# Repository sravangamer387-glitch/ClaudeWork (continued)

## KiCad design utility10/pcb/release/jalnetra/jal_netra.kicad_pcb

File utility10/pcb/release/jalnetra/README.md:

# Jal-Netra ultrasonic flow main board (rev A)

Jal-Netra main board: STM32G431 transit-time measurement (bridge-driven piezo, input mux, two-stage low-noise receive chain, gain select, 12-bit 4 MS/s ADC), USB-C powered, OLED/UART/SWD.

**Status: engineering release, software-verified only (ERC on the netlist, KiCad DRC, netlist cross-check, SPICE where noted). Not yet built, not reviewed by a second engineer, not certified.**

## Specification
- Board 86 x 66 mm, 2 layers, 1.6 mm FR-4, 1 oz copper, rounded corners R2.5 mm, 4 x M2.5 mounting holes, 2 fiducials.
- Rules used: min track 0.2 mm (power 0.4 mm), min clearance 0.15 mm, via 0.6/0.3 mm, GND pour on both layers, 128 stitching vias.
- Finish: ENIG recommended (HASL lead-free acceptable); green mask, white silk; IPC class 2.
- 78 parts, 51 nets.

## Circuit description
- **Transmit:** TIM3 channels on PA6/PA4 (transducer A) and PB0/PB1 (transducer B) generate a 6-cycle 1 MHz burst; the second pin of each pair is inverted for bridge drive (6.6 Vpp). 22 ohm series resistors protect the pins; on receive one leg is held low by its timer pin and the other is high-impedance.
- **Receive:** 10 nF + 1 k tap from the transducer's high leg, BAV99 clamp to the rails, TS5A3159 selects transducer A or B into LNA1 (OPA356, x10.2) and LNA2 (x10.2); TS5A3159 U7 selects 20 dB or 40 dB into a 33 ohm / 22 pF filter and ADC1 (PA0). Mid-supply bias 1.65 V from AVDD (ferrite-filtered 3.3 V).
- **Rest:** STM32G431CBT6 with 8 MHz crystal, SWD header, boot0 pull-down, USB-C power-only (5.1 k CC, PTC, TVS), AP2112K-3.3, OLED and UART headers, buzzer, LED, test button, test points on the receive chain.

### Simulation: `../../jal-netra/sim/lna_results.txt`
```
SPICE (ngspice) of the receive chain, source impedance 270 ohm (piezo at 1 MHz), OPA356-class model (A0 1e5, GBW 200 MHz):
stage 1 gain at 1 MHz        = 20.1 dB (target 20 dB)
stage 1 + 2 gain at 1 MHz   = 40.9 dB (target 40 dB)
stage 1 upper -3 dB          = 20 MHz
stage 1 + 2 band (-3 dB)      = 1.5 kHz ... 14 MHz
```

## Power
MCU 170 MHz about 35 mA while measuring (0.5 s per measurement), LNAs 2 x 8 mA: USB powered only (about 0.1 W average with a 10 s idle period).

## Verification
| Check | Result |
|---|---|
| Electrical rule check on the netlist (own ERC: unconnected pins, single-pin nets, output conflicts, unpowered supplies, symbol/footprint pin match) | 0 errors, 0 warnings |
| KiCad DRC | 0 errors, 0 warnings; unconnected pads: 0 |
| Schematic netlist equals PCB netlist | yes |
| Router failures | 0 |
| 3D STEP export | yes |
| Independent Gerber parse (gerbonara): layers parsed, outline size equals the design | 9 layers, outline [86.1, 66.1] mm, match |

Enclosure (prototype shell for 3D printing): outer 91.2 x 71.2 x 20.6 mm, collision/opening check: pass

## Bill of materials
| Ref | Value | Footprint | Manufacturer part | LCSC # | LCSC status |
|---|---|---|---|---|---|
| U1 | STM32G431CBT6 | LQFP-48_7x7mm_P0.5mm | STM32G431CBT6 (LQFP-48) | C529355 | verified |
| U4 | TS5A3159 | SOT-363_SC-70-6 | TI TS5A3159DCKR | C46388 | verified |
| U5 | OPA356 | SOT-23-5 | TI OPA356AIDBVR | C183100 | verified |
| U6 | OPA356 | SOT-23-5 | TI OPA356AIDBVR | C183100 | verified |
| U7 | TS5A3159 | SOT-363_SC-70-6 | TI TS5A3159DCKR | C46388 | verified |
| U3 | AP2112K-3.3 | SOT-23-5 | Diodes AP2112K-3.3TRG1 (from the LCSC datasheet link) | C51118 | verified |
| FB1 | BLM18 600R | L_0603_1608Metric | Murata BLM18AG601SN1D | C19330 | verified |
| Y1 | 8 MHz | Crystal_SMD_3225-4Pin_3.2x2.5mm | YXC X32258MOB4SI 8 MHz 12 pF 3225 (matches the 15 pF load caps) | C2682775 | verified |
| D5 | BAV99 | SOT-23 | JSCJ BAV99 | C68983 | verified |
| D6 | BAV99 | SOT-23 | JSCJ BAV99 | C68983 | verified |
| J6 | Transducer A (BTL) | JST_PH_B2B-PH-K_1x02_P2.00mm_Vertical | JST B2B-PH-K-S(LF)(SN) | C131337 | verified |
| J7 | Transducer B (BTL) | JST_PH_B2B-PH-K_1x02_P2.00mm_Vertical | JST B2B-PH-K-S(LF)(SN) | C131337 | verified |
| R30 | 22 | R_0603_1608Metric | UNI-ROYAL 0603WAF220JT5E | C23345 | verified |
| R31 | 22 | R_0603_1608Metric | UNI-ROYAL 0603WAF220JT5E | C23345 | verified |
| R32 | 22 | R_0603_1608Metric | UNI-ROYAL 0603WAF220JT5E | C23345 | verified |
| R33 | 22 | R_0603_1608Metric | UNI-ROYAL 0603WAF220JT5E | C23345 | verified |
| C20 | 10n | C_0603_1608Metric | Samsung CL10B103KB8NNNC 0603 10nF X7R 50V | C1589 | verified |
| R35 | 1k | R_0603_1608Metric | 0603 1k 1% | C21190 | verified |
| C21 | 10n | C_0603_1608Metric | Samsung CL10B103KB8NNNC 0603 10nF X7R 50V | C1589 | verified |
| R36 | 1k | R_0603_1608Metric | 0603 1k 1% | C21190 | verified |
| C22 | 100n | C_0603_1608Metric | Samsung CL10B104KB8NNNC 0603 100nF X7R 50V | C1591 | verified |
| C23 | 100n | C_0603_1608Metric | Samsung CL10B104KB8NNNC 0603 100nF X7R 50V | C1591 | verified |
| C24 | 100n | C_0603_1608Metric | Samsung CL10B104KB8NNNC 0603 100nF X7R 50V | C1591 | verified |
| C25 | 1u | C_0603_1608Metric | 0603 1uF X7R | C15849 | verified |
| R10 | 10k | R_0603_1608Metric | 0603 10k 1% | C25804 | verified |
| R11 | 10k | R_0603_1608Metric | 0603 10k 1% | C25804 | verified |
| C27 | 1u | C_0603_1608Metric | 0603 1uF X7R | C15849 | verified |
| C28 | 10n | C_0603_1608Metric | Samsung CL10B103KB8NNNC 0603 10nF X7R 50V | C1589 | verified |
| R12 | 100k | R_0603_1608Metric | 0603 100k 1% | C25803 | verified |
| R13 | 2.2k | R_0603_1608Metric | 0603 2.2k 1% | C4190 | verified |
| R14 | 240 | R_0603_1608Metric | UNI-ROYAL 0603WAF2400T5E (JLCPCB listing) | C23350 | verified |
| C29 | 1u | C_0603_1608Metric | 0603 1uF X7R | C15849 | verified |
| R15 | 0 | R_0603_1608Metric | UNI-ROYAL 0603WAF0000T5E | C21189 | verified |
| C30 | 10n | C_0603_1608Metric | Samsung CL10B103KB8NNNC 0603 10nF X7R 50V | C1589 | verified |
| R16 | 100k | R_0603_1608Metric | 0603 100k 1% | C25803 | verified |
| R17 | 1k | R_0603_1608Metric | 0603 1k 1% | C21190 | verified |
| R18 | 100 | R_0603_1608Metric | UNI-ROYAL 0603WAF1000T5E | C22775 | verified |
| C31 | 1u | C_0603_1608Metric | 0603 1uF X7R | C15849 | verified |
| R19 | 0 | R_0603_1608Metric | UNI-ROYAL 0603WAF0000T5E | C21189 | verified |
| R20 | 33 | R_0603_1608Metric | UNI-ROYAL 0603WAF330JT5E | C23140 | verified |
| C32 | 22p | C_0603_1608Metric | Samsung CL10C220JB8NNNC C0G | C1653 | verified |
| C1 | 100n | C_0603_1608Metric | Samsung CL10B104KB8NNNC 0603 100nF X7R 50V | C1591 | verified |
| C2 | 100n | C_0603_1608Metric | Samsung CL10B104KB8NNNC 0603 100nF X7R 50V | C1591 | verified |
| C3 | 100n | C_0603_1608Metric | Samsung CL10B104KB8NNNC 0603 100nF X7R 50V | C1591 | verified |
| C4 | 100n | C_0603_1608Metric | Samsung CL10B104KB8NNNC 0603 100nF X7R 50V | C1591 | verified |
| C33 | 100n | C_0603_1608Metric | Samsung CL10B104KB8NNNC 0603 100nF X7R 50V | C1591 | verified |
| C34 | 4.7u | C_0603_1608Metric | Samsung CL10A475KP8NNNC X5R 10V | C1705 | verified |
| C35 | 15p | C_0603_1608Metric | Samsung CL10C150JB8NNNC C0G | C1644 | verified |
| C36 | 15p | C_0603_1608Metric | Samsung CL10C150JB8NNNC C0G | C1644 | verified |
| R21 | 10k | R_0603_1608Metric | 0603 10k 1% | C25804 | verified |
| R22 | 10k | R_0603_1608Metric | 0603 10k 1% | C25804 | verified |
| C37 | 100n | C_0603_1608Metric | Samsung CL10B104KB8NNNC 0603 100nF X7R 50V | C1591 | verified |
| C38 | 1u | C_0603_1608Metric | 0603 1uF X7R | C15849 | verified |
| C39 | 1u | C_0603_1608Metric | 0603 1uF X7R | C15849 | verified |
| J4 | OLED I2C | JST_PH_B4B-PH-K_1x04_P2.00mm_Vertical | JST B4B-PH-K-S(LF)(SN) | C131334 | verified |
| R23 | 4.7k | R_0603_1608Metric | 0603 4.7k 1% | C23162 | verified |
| R24 | 4.7k | R_0603_1608Metric | 0603 4.7k 1% | C23162 | verified |
| J5 | UART host / BLE | JST_PH_B4B-PH-K_1x04_P2.00mm_Vertical | JST B4B-PH-K-S(LF)(SN) | C131334 | verified |
| J3 | SWD | PinHeader_2x03_P2.54mm_Vertical | HCTL PZ254-2-03-Z-8.5 (ZHOURI C5116479 had only 340 in stock) | C2894964 | verified |
| SW2 | Test / zero | SW_SPST_B3U-1000P | Omron B3U-1000P | C231329 | verified |
| TP1 | TP | TestPoint_Pad_D1.5mm |  |  |  |
| TP2 | TP | TestPoint_Pad_D1.5mm |  |  |  |
| TP3 | TP | TestPoint_Pad_D1.5mm |  |  |  |
| TP4 | TP | TestPoint_Pad_D1.5mm |  |  |  |
| TP5 | TP | TestPoint_Pad_D1.5mm |  |  |  |
| TP6 | TP | TestPoint_Pad_D1.5mm |  |  |  |
| J1 | USB-C 5V | USB_C_Receptacle_HRO_TYPE-C-31-M-12 | TYPE-C-31-M-12 | C165948 | verified |
| F1 | PTC 500mA | Fuse_1206_3216Metric | Littelfuse 1206L050YR (6 V) | C163512 | verified |
| D3 | SMAJ5.0A | D_SMA | Littelfuse SMAJ5.0A | C83329 | verified |
| R1 | 5.1k | R_0603_1608Metric | 0603 5.1k 1% | C23186 | verified |
| R2 | 5.1k | R_0603_1608Metric | 0603 5.1k 1% | C23186 | verified |
| C5 | 10u | C_0805_2012Metric | 0805 10uF X5R | C15850 | verified |
| BZ1 | Buzzer | Buzzer_12x9.5RM7.6 | YUEXIN KC1206 16 ohm passive magnetic 12x9.5 mm (2048 Hz) | C781869 | verified |
| Q1 | MMBT3904 | SOT-23 | MMBT3904 | C20526 | verified |
| D2 | 1N4148WS | D_SOD-323 | 1N4148WS | C2128 | verified |
| R7 | 1k | R_0603_1608Metric | 0603 1k 1% | C21190 | verified |
| D1 | Green | LED_0603_1608Metric | Hubei KENTO KT-0603YG yellow-green 570 nm, Vf about 2 V (lights well from 3.3 V with 1 k; the Everlight 19-217 green was out of stock) | C2289 | verified |
| R5 | 1k | R_0603_1608Metric | 0603 1k 1% | C21190 | verified |

`verified` = LCSC number confirmed by web search on 2026-10-31/11-01; `memory` = from my recollection, **check on lcsc.com before ordering**; empty = no number chosen (through-hole connectors, switches, buzzer, test points: hand-assembled or chosen by the buyer). `*_JLC_BOM.csv` / `*_JLC_CPL.csv` list only the parts with an LCSC number; JLCPCB rotation corrections (CPL) must be checked in their viewer.

## Assembly notes
- Reflow (JLCPCB SMT): all SMD parts with an LCSC number. Hand-solder: JST connectors, pin headers, buzzer, switches, test points as listed in the BOM. Fiducials and mounting holes are in the Gerbers.
- Polarity: LED cathode toward GND (silk marks), electrolytic none, diode D2 cathode to +V, Q2 orientation as footprint (SOT-23 pin 1 = gate).
- Programming: ISP header J2 (pin 1 = MISO, square pad). Flash the matching image from `utility10/firmware/release/`: Seeti Counter `4MHz/seeti_prod.hex` (production firmware: timer-triggered 16 kS/s ADC, scan mode to find the real whistle frequency, battery check), Rain Alert `8MHz/rain_alert.hex`, Bijli Meter Reader `8MHz/bijli_meter.hex` (demo-grade firmware, to be hardened).

## Bring-up and test
1. USB-C 5 V: +3V3 = 3.3 V, AVDD = 3.28 V, VMID = 1.64 V.
2. Flash over SWD; with the spool dry nothing should be received (amplitude near zero); fill with water: a burst of amplitude A appears at ADC_IN 40.5 us after the transmit edge (TP5).
3. Follow `jal-netra/docs/TEST_PLAN.md` gates 1-3.

## Files
`1_fabrication/` Gerber + drill zip (upload to JLCPCB/any fab), fab notes, copper plot
`2_assembly/` JLC BOM + CPL (SMD parts JLC assembles), full BOM with LCSC numbers for every part, pick-and-place, assembly drawing
`3_design/` KiCad 7 project (pcb, schematic, libs), netlist, STEP model, schematic PDF, renders
`4_enclosure/` printable base and lid STL
`5_verification/` DRC, ERC, verification and readiness reports

## Known limits and review checklist
- Layout was produced by a custom router and software placement; a human layout review (analog routing, ground returns, creepage, connector mechanics, silkscreen) is still required.
- Not verified: EMC, ESD (apart from TVS parts where fitted), thermal, real component tolerances, supplier stock/price, assembly house design-for-manufacture check (run JLCPCB's DFM check on the Gerbers).
- Firmware thresholds are placeholders to be calibrated on prototypes.

## Manufacturing readiness (automatic check)

| Check | Result |
|---|---|
| gerber layers and drill present | PASS |
| drc errors 0 | PASS |
| unconnected 0 | PASS |
| netlist matches schematic | PASS |
| erc errors 0 | PASS |
| independent gerber check clean | PASS |
| every part has lcsc number | PASS |
| every lcsc number verified | PASS |
| cpl rows equal jlc bom parts | PASS |
| step model | PASS |
| KiCad DRC warnings | 0 |
| **Order ready** | **YES** |

Order steps: (1) upload `1_fabrication/*_gerbers.zip`; (2) for assembly upload `2_assembly/*_JLC_BOM.csv` and `*_JLC_CPL.csv`, check the 3D/rotation preview for every polarised part (diodes, ICs, LEDs, electrolytics) because CPL rotations are generated, not hand-checked; (3) buy the through-hole parts listed in `*_BOM_full.csv` marked hand/THT and solder them; (4) re-check stock and the exact LCSC listing for every line before paying.

Limits: the layout is software-generated and has not been reviewed by a PCB engineer; no prototype has been built; the first batch should be treated as a prototype run (order 5 boards).

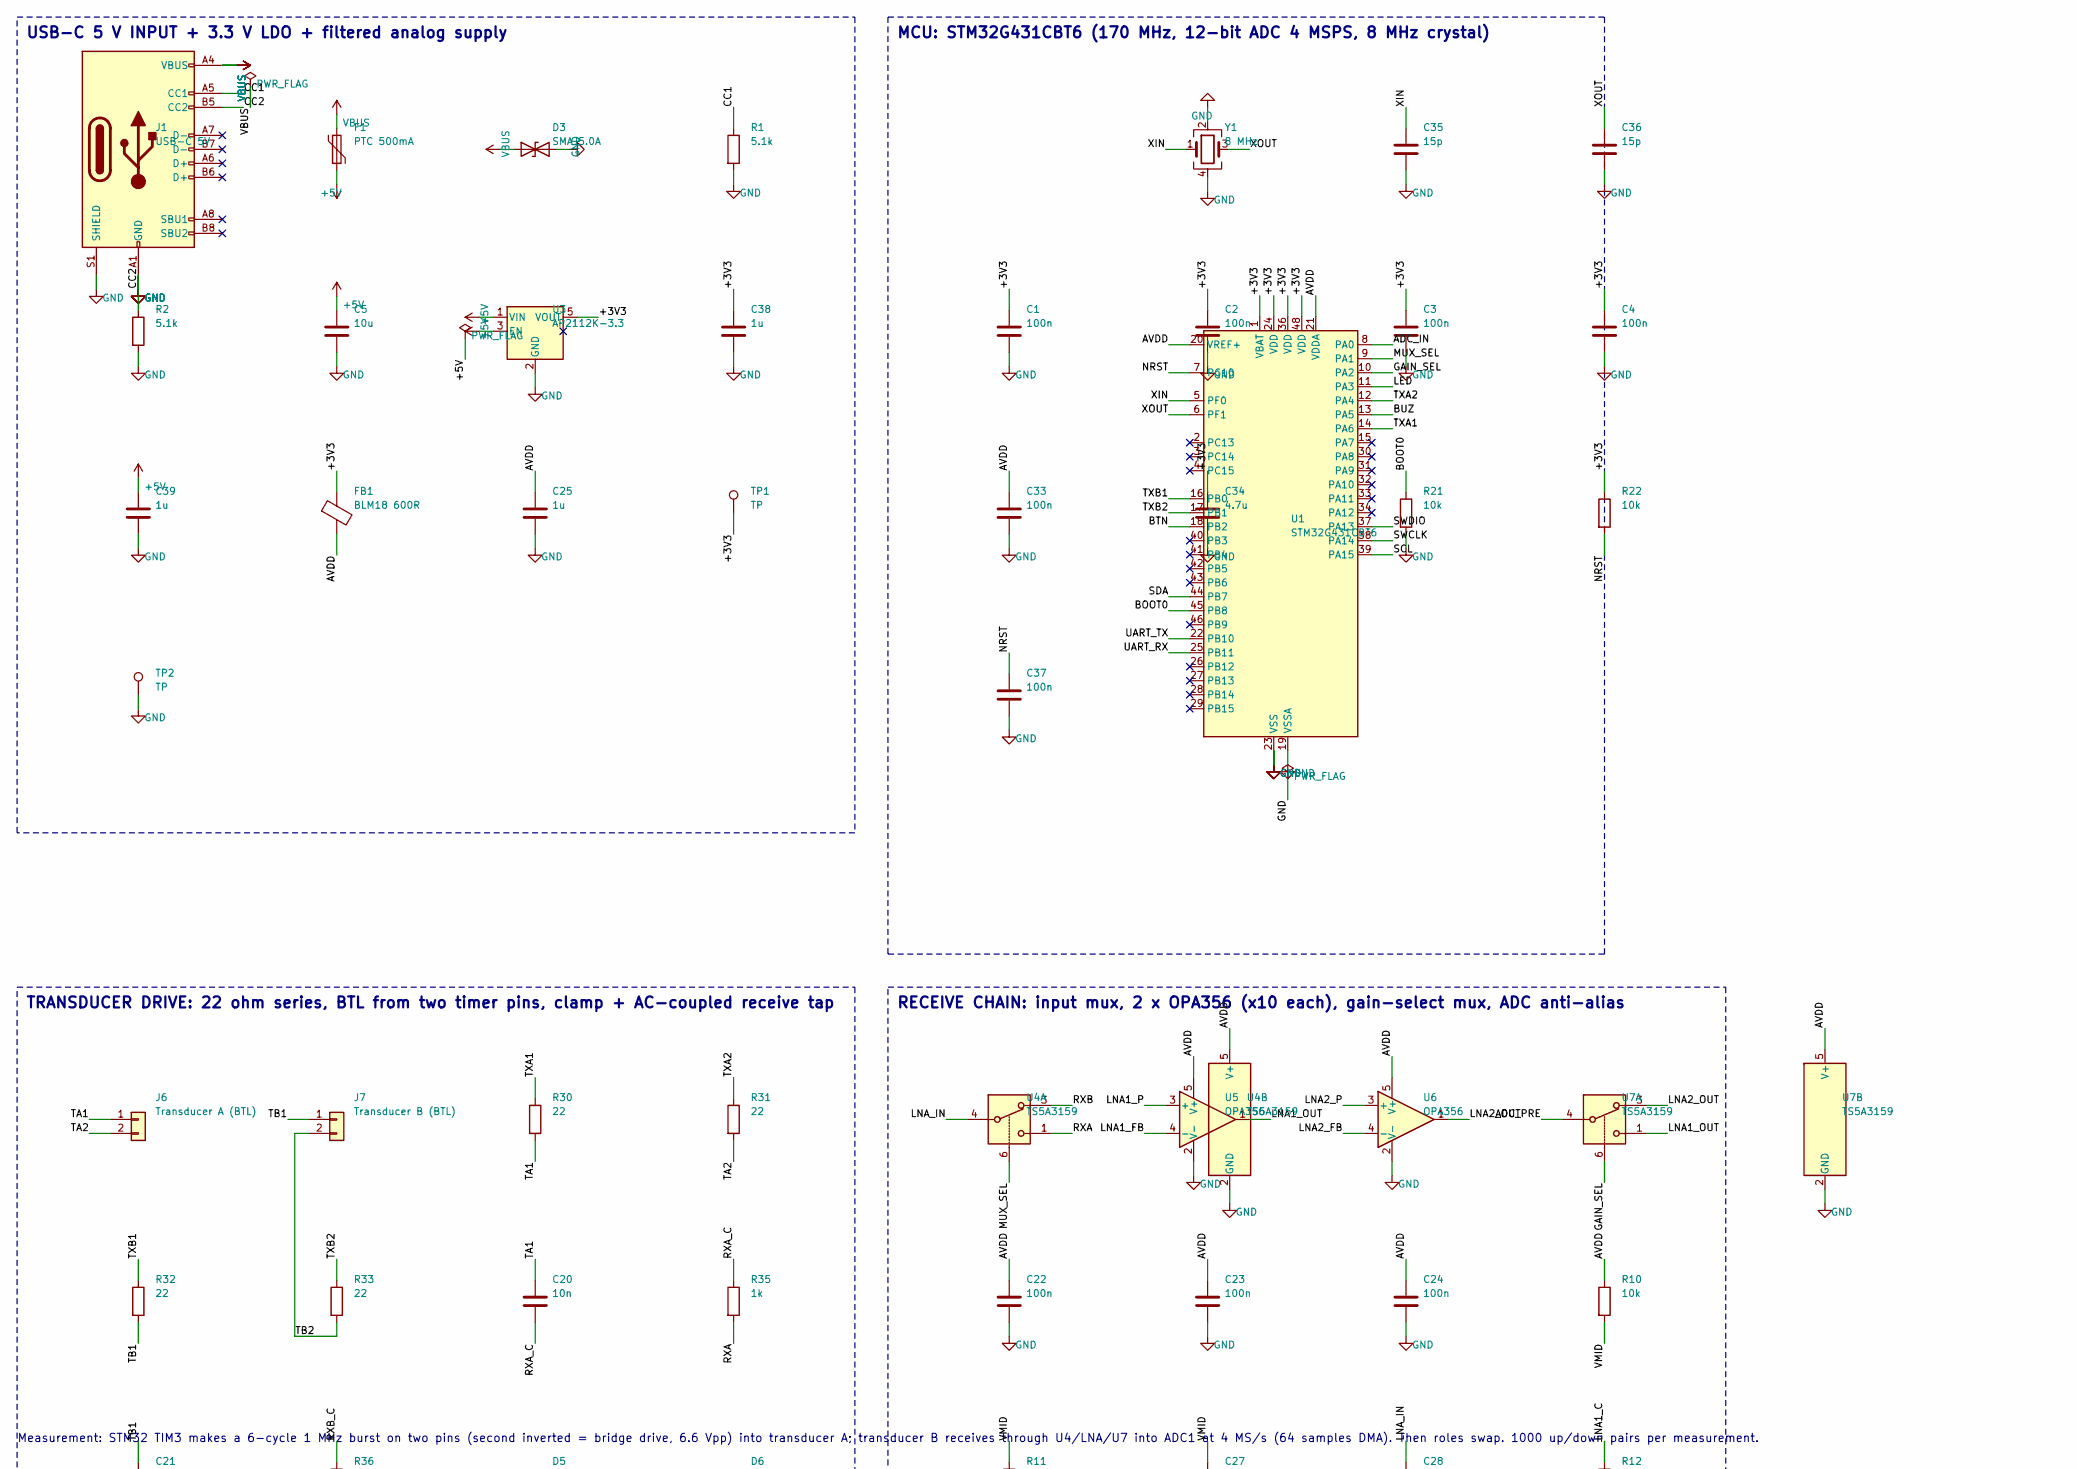
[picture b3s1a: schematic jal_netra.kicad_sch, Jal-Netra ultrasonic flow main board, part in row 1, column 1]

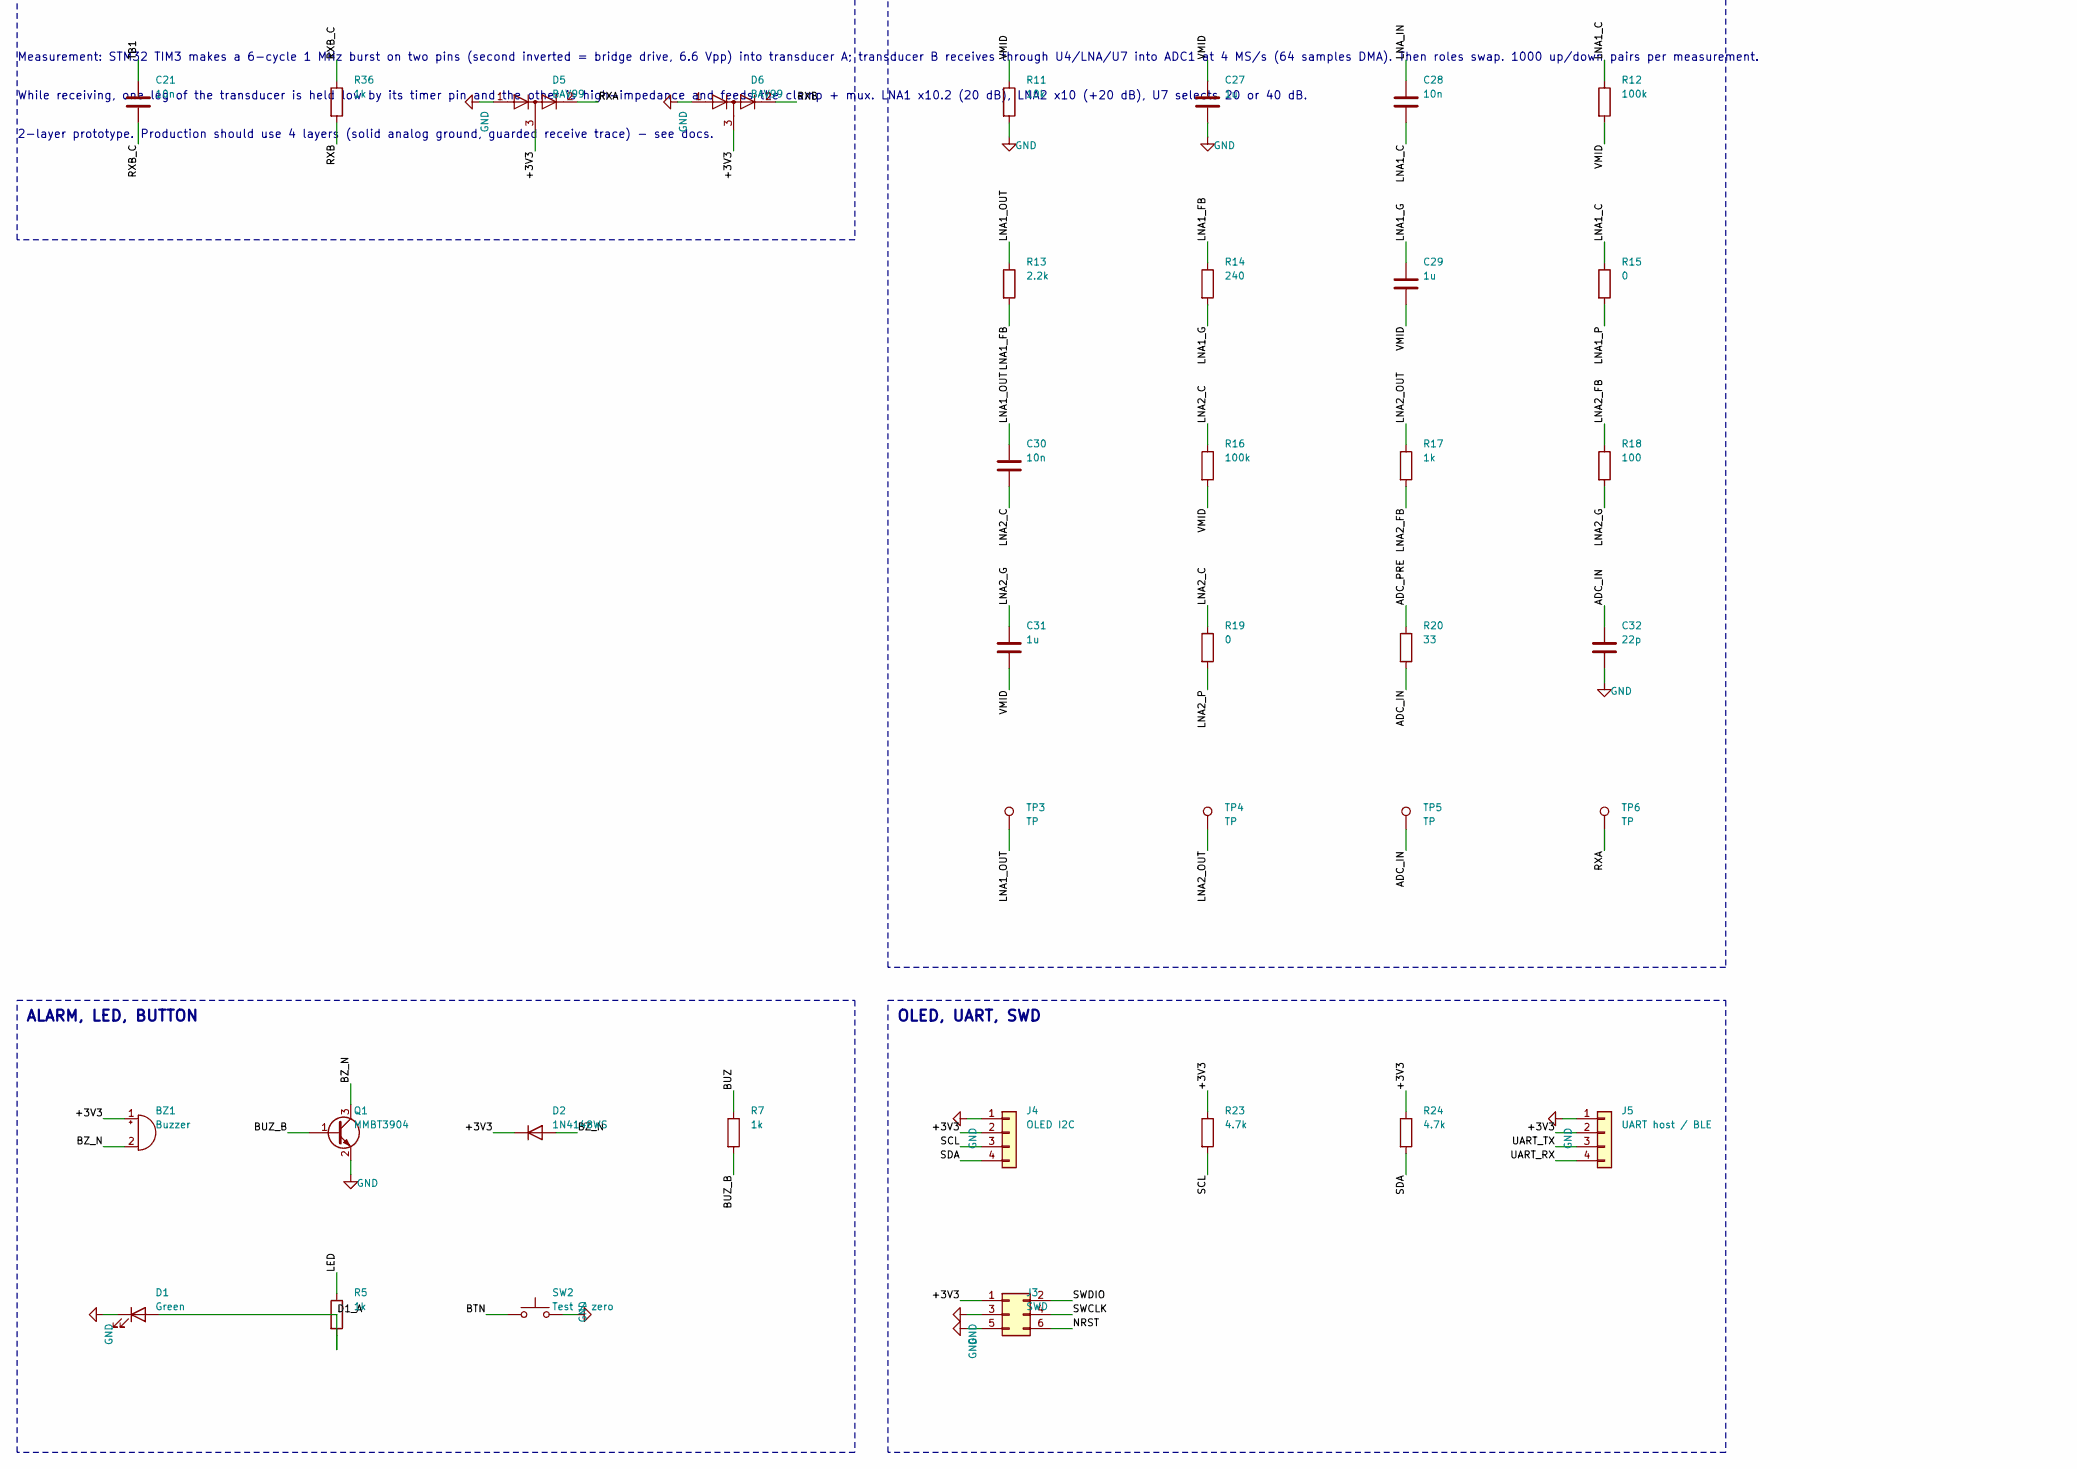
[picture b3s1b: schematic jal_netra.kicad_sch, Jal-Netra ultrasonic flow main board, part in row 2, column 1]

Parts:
BZ1: Buzzer; Buzzer_12x9.5RM7.6
C1, C2, C3, C4, C22, C23, C24, C33, C37: 100n; C_0603_1608Metric
C5: 10u; C_0805_2012Metric
C20, C21, C28, C30: 10n; C_0603_1608Metric
C25, C27, C29, C31, C38, C39: 1u; C_0603_1608Metric
C32: 22p; C_0603_1608Metric
C34: 4.7u; C_0603_1608Metric
C35, C36: 15p; C_0603_1608Metric
D1: Green; LED_0603_1608Metric
D2: 1N4148WS; D_SOD-323
D3: SMAJ5.0A; D_SMA
D5, D6: BAV99; SOT-23
F1: PTC 500mA; Fuse_1206_3216Metric
FB1: BLM18 600R; L_0603_1608Metric
J1: USB-C 5V; USB_C_Receptacle_HRO_TYPE-C-31-M-12
J3: SWD; PinHeader_2x03_P2.54mm_Vertical
J4: OLED I2C; JST_PH_B4B-PH-K_1x04_P2.00mm_Vertical
J5: UART host / BLE; JST_PH_B4B-PH-K_1x04_P2.00mm_Vertical
J6: Transducer A (BTL); JST_PH_B2B-PH-K_1x02_P2.00mm_Vertical
J7: Transducer B (BTL); JST_PH_B2B-PH-K_1x02_P2.00mm_Vertical
Q1: MMBT3904; SOT-23
R1, R2: 5.1k; R_0603_1608Metric
R5, R7, R17, R35, R36: 1k; R_0603_1608Metric
R10, R11, R21, R22: 10k; R_0603_1608Metric
R12, R16: 100k; R_0603_1608Metric
R13: 2.2k; R_0603_1608Metric
R14: 240; R_0603_1608Metric
R15, R19: 0; R_0603_1608Metric
R18: 100; R_0603_1608Metric
R20: 33; R_0603_1608Metric
R23, R24: 4.7k; R_0603_1608Metric
R30, R31, R32, R33: 22; R_0603_1608Metric
SW2: Test / zero; SW_SPST_B3U-1000P
TP1, TP2, TP3, TP4, TP5, TP6: TP; TestPoint_Pad_D1.5mm
U1: STM32G431CBT6; LQFP-48_7x7mm_P0.5mm
U3: AP2112K-3.3; SOT-23-5
U4, U7: TS5A3159; SOT-363_SC-70-6
U5, U6: OPA356; SOT-23-5
Y1: 8 MHz; Crystal_SMD_3225-4Pin_3.2x2.5mm

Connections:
+3V3: BZ1.1 (+), C1.1, C2.1, C3.1, C4.1, C34.1, C38.1, D2.1 (K), D5.3 (K), D6.3 (K), FB1.1, J3.1, J4.2, J5.2, R22.1, R23.1, R24.1, TP1.1, U1.1 (VBAT), U1.24 (VDD), U1.36 (VDD), U1.48 (VDD), U3.5 (VOUT)
+5V: C5.1, C39.1, F1.2, U3.1 (VIN), U3.3 (EN)
ADC_IN: C32.1, R20.2, TP5.1, U1.8 (PA0)
ADC_PRE: R20.1, U7.4
AVDD: C22.1, C23.1, C24.1, C25.1, C33.1, FB1.2, R10.1, U1.20 (VREF+), U1.21 (VDDA), U4.5 (V+), U5.5 (V+), U6.5 (V+), U7.5 (V+)
BOOT0: R21.1, U1.45 (PB8)
BTN: SW2.1, U1.18 (PB2)
BUZ: R7.1, U1.13 (PA5)
BUZ_B: Q1.1 (B), R7.2
BZ_N: BZ1.2 (-), D2.2 (A), Q1.3 (C)
CC1: J1.A5 (CC1), R1.1
D1_A: D1.2 (A), R5.2
GAIN_SEL: U1.10 (PA2), U7.6
LED: R5.1, U1.11 (PA3)
LNA1_C: C28.2, R12.1, R15.1
LNA1_FB: R13.2, R14.1, U5.4 (-)
LNA1_G: C29.1, R14.2
LNA1_OUT: C30.1, R13.1, TP3.1, U5.1, U7.1
LNA1_P: R15.2, U5.3 (+)
LNA2_C: C30.2, R16.1, R19.1
LNA2_FB: R17.2, R18.1, U6.4 (-)
LNA2_G: C31.1, R18.2
LNA2_OUT: R17.1, TP4.1, U6.1, U7.3
LNA2_P: R19.2, U6.3 (+)
LNA_IN: C28.1, U4.4
MUX_SEL: U1.9 (PA1), U4.6
NRST: C37.1, J3.6, R22.2, U1.7 (PG10)
RXA: D5.2 (A), R35.2, TP6.1, U4.1
RXA_C: C20.2, R35.1
RXB: D6.2 (A), R36.2, U4.3
RXB_C: C21.2, R36.1
SCL: J4.3, R23.2, U1.39 (PA15)
SDA: J4.4, R24.2, U1.44 (PB7)
SWCLK: J3.4, U1.38 (PA14)
SWDIO: J3.2, U1.37 (PA13)
TA1: C20.1, J6.1, R30.2
TA2: J6.2, R31.2
TB1: C21.1, J7.1, R32.2
TB2: J7.2, R33.2
TXA1: R30.1, U1.14 (PA6)
TXA2: R31.1, U1.12 (PA4)
TXB1: R32.1, U1.16 (PB0)
TXB2: R33.1, U1.17 (PB1)
UART_RX: J5.4, U1.25 (PB11)
UART_TX: J5.3, U1.22 (PB10)
VBUS: D3.1 (A1), F1.1, J1.A4 (VBUS), J1.A9 (VBUS), J1.B4 (VBUS), J1.B9 (VBUS)
VMID: C27.1, C29.2, C31.2, R10.2, R11.1, R12.2, R16.2
XIN: C35.1, U1.5 (PF0), Y1.1
XOUT: C36.1, U1.6 (PF1), Y1.3

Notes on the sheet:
USB-C 5 V INPUT + 3.3 V LDO + filtered analog supply
MCU: STM32G431CBT6 (170 MHz, 12-bit ADC 4 MSPS, 8 MHz crystal)
TRANSDUCER DRIVE: 22 ohm series, BTL from two timer pins, clamp + AC-coupled receive tap
RECEIVE CHAIN: input mux, 2 x OPA356 (x10 each), gain-select mux, ADC anti-alias
ALARM, LED, BUTTON
OLED, UART, SWD
Measurement: STM32 TIM3 makes a 6-cycle 1 MHz burst on two pins (second inverted = bridge drive, 6.6 Vpp) into transducer A; transducer B receives through U4/LNA/U7 into ADC1 at 4 MS/s (64 samples DMA). Then roles swap. 1000 up/down pairs per measurement.
While receiving, one leg of the transducer is held low by its timer pin and the other is high-impedance and feeds the clamp + mux. LNA1 x10.2 (20 dB), LNA2 x10 (+20 dB), U7 selects 20 or 40 dB.
2-layer prototype. Production should use 4 layers (solid analog ground, guarded receive trace) - see docs.

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
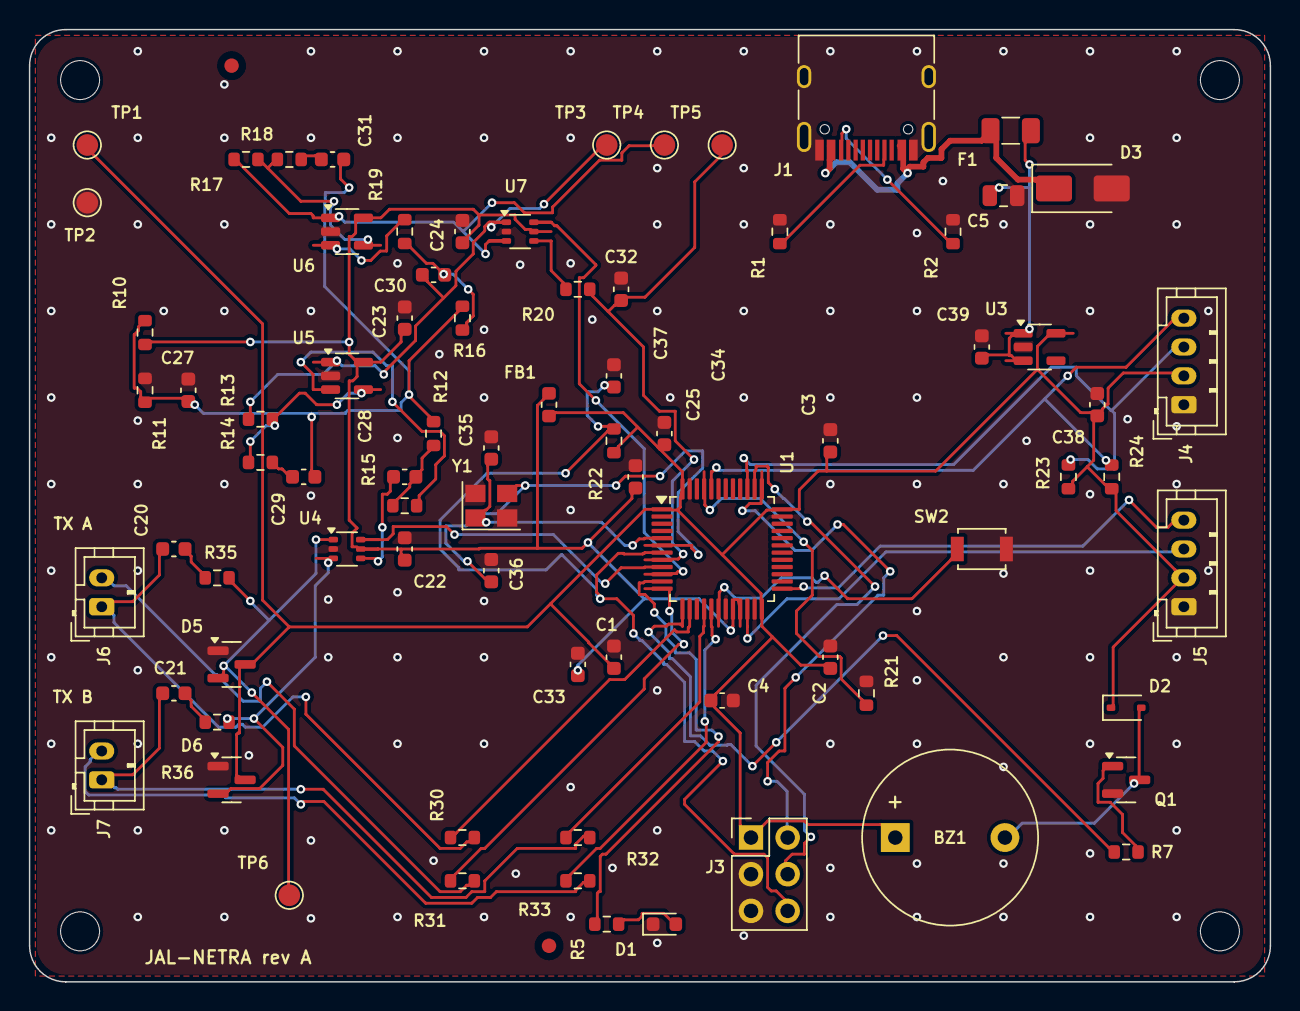
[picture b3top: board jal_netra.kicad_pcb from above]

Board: 2 copper layers, 86.0 x 66.0 mm, 84 parts (0 on the bottom side), 51 nets.

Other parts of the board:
FID1, FID2: Fiducial; Fiducial_1mm_Mask2mm
H1, H2, H3, H4: M2.5; MountingHole_2.7mm_M2.5
